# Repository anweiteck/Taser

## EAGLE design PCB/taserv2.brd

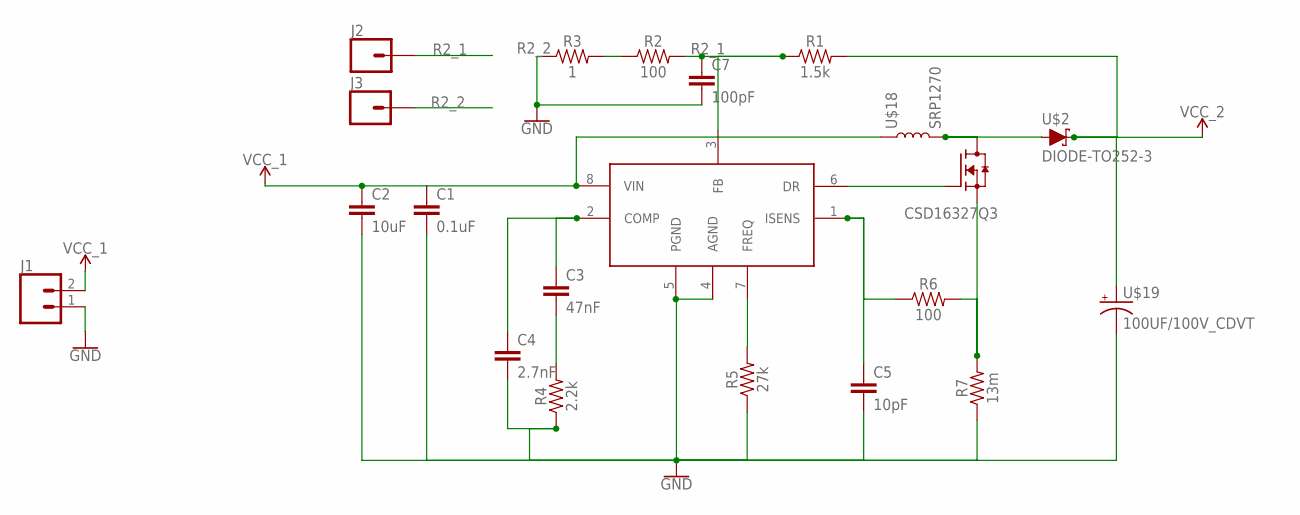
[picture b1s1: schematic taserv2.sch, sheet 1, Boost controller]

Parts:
C1: 0.1uF; 0603
C2: 10uF; 0603
C3: 47nF; 1206
C4: 2.7nF; 0603
C5: 10pF; 0603
C7: 100pF; 0603
J1: CONN_02LOCK; 1X02_LOCK
J2, J3: CONN_01; 1X01
Q1: CSD16327Q3; TRANS_CSD16327Q3
R1: 1.5k; 0603
R2, R6: 100; 0603
R3: 1; 0603
R4: 2.2k; 0603
R5: 27k; 0603
R7: 13m; 0603
U$1: LM3478; SOIC-8
U$2: DIODE-TO252-3; DPAK
U$18: SRP1270
U$19: 100UF/100V_CDVT

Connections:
GND: C1.2, C2.2, C4.2, C5.2, J1.1, R4.1, R5.1, R7.1, U$1.4 (AGND), U$1.5 (PGND), U$19.P$2 (-); also elsewhere on the board
unnamed: C3.1, C4.1, U$1.2 (COMP)
unnamed: C3.2, R4.2
unnamed: R5.2, U$1.7 (FREQ)
unnamed: R2.1, R3.2
unnamed: Q1.4 (G), U$1.6 (DR)
unnamed: Q1.1 (S), Q1.2 (S), Q1.3 (S), R6.2, R7.2
unnamed: C5.1, R6.1, U$1.1 (ISENS)
unnamed: Q1.5-8 (D), U$2.1 (A), U$2.3 (A), U$18.P$2 (2)
R2_1: C7.1, J2.1, R1.1, R2.2, U$1.3 (FB)
R2_2: C7.2, J3.1, R3.1
VCC_1: C1.1, C2.1, J1.2, U$1.8 (VIN), U$18.P$1 (1)
VCC_2: R1.2, U$2.4 (C), U$19.P$1 (+); also elsewhere on the board

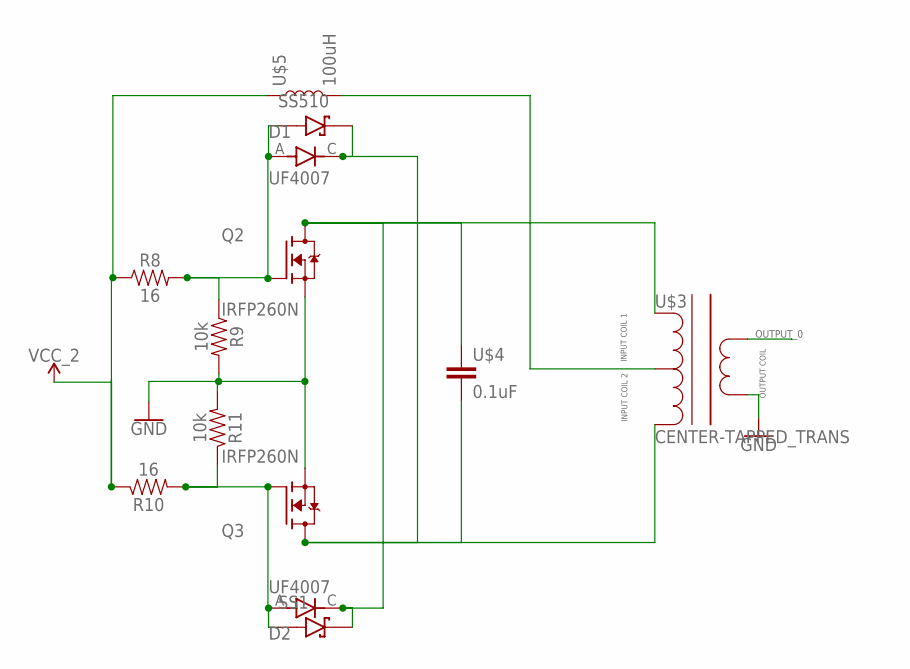
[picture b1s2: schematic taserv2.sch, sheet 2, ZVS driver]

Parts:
D1, D2: UF4007; DIOAD1036W78L520D274
Q2, Q3: IRFP260N; TO545P1560X500X2460-3
R8, R10: 16; 0603
R9, R11: 10k; 0603
SS1, SS510: MBRS340T3G; DIOM7959X261N
U$3: CENTER-TAPPED_TRANS
U$4: 0.1uF; MKP_CAP
U$5: 100uH; 1X04_LOCK

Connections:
GND: Q2.3 (S), Q3.3 (S), R9.2, R11.2, U$3.5; also elsewhere on the board
unnamed: D2.C (K), Q2.2 (D), SS1.C (K), U$3.3, U$4.1
unnamed: D1.A, Q2.1 (G), R8.2, R9.1, SS510.A
unnamed: D2.A, Q3.1 (G), R10.2, R11.1, SS1.A
unnamed: D1.C (K), Q3.2 (D), SS510.C (K), U$3.1, U$4.5 (2)
unnamed: U$3.2, U$5.4 (2)
OUTPUT_0: U$3.4; also elsewhere on the board
VCC_2: R8.1, R10.1, U$5.1; also elsewhere on the board

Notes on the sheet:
INPUT COIL 2
INPUT COIL 1
OUTPUT COIL

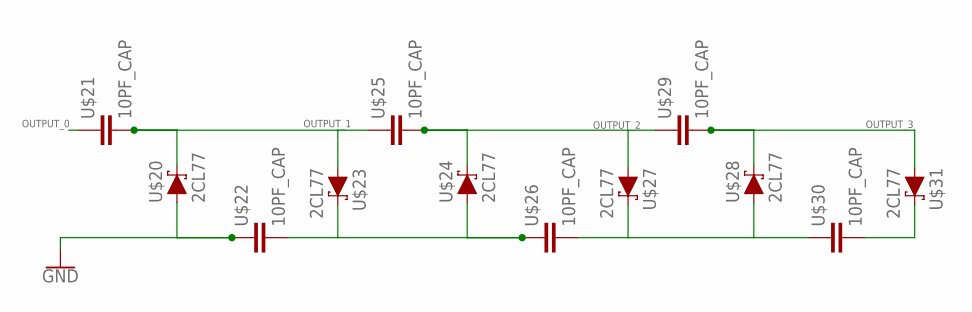
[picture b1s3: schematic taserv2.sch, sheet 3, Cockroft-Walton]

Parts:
U$20, U$23, U$24, U$27, U$28, U$31: 2CL77
U$21, U$22, U$25, U$26, U$29, U$30: 10PF_CAP

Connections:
GND: U$20.1 (A), U$22.1; also elsewhere on the board
unnamed: U$22.4 (2), U$23.4 (C), U$24.1 (A), U$26.1
unnamed: U$26.4 (2), U$27.4 (C), U$28.1 (A), U$30.1
unnamed: U$30.4 (2), U$31.4 (C)
OUTPUT_0: U$21.1; also elsewhere on the board
OUTPUT_1: U$20.4 (C), U$21.4 (2), U$23.1 (A), U$25.1
OUTPUT_2: U$24.4 (C), U$25.4 (2), U$27.1 (A), U$29.1
OUTPUT_3: U$28.4 (C), U$29.4 (2), U$31.1 (A)

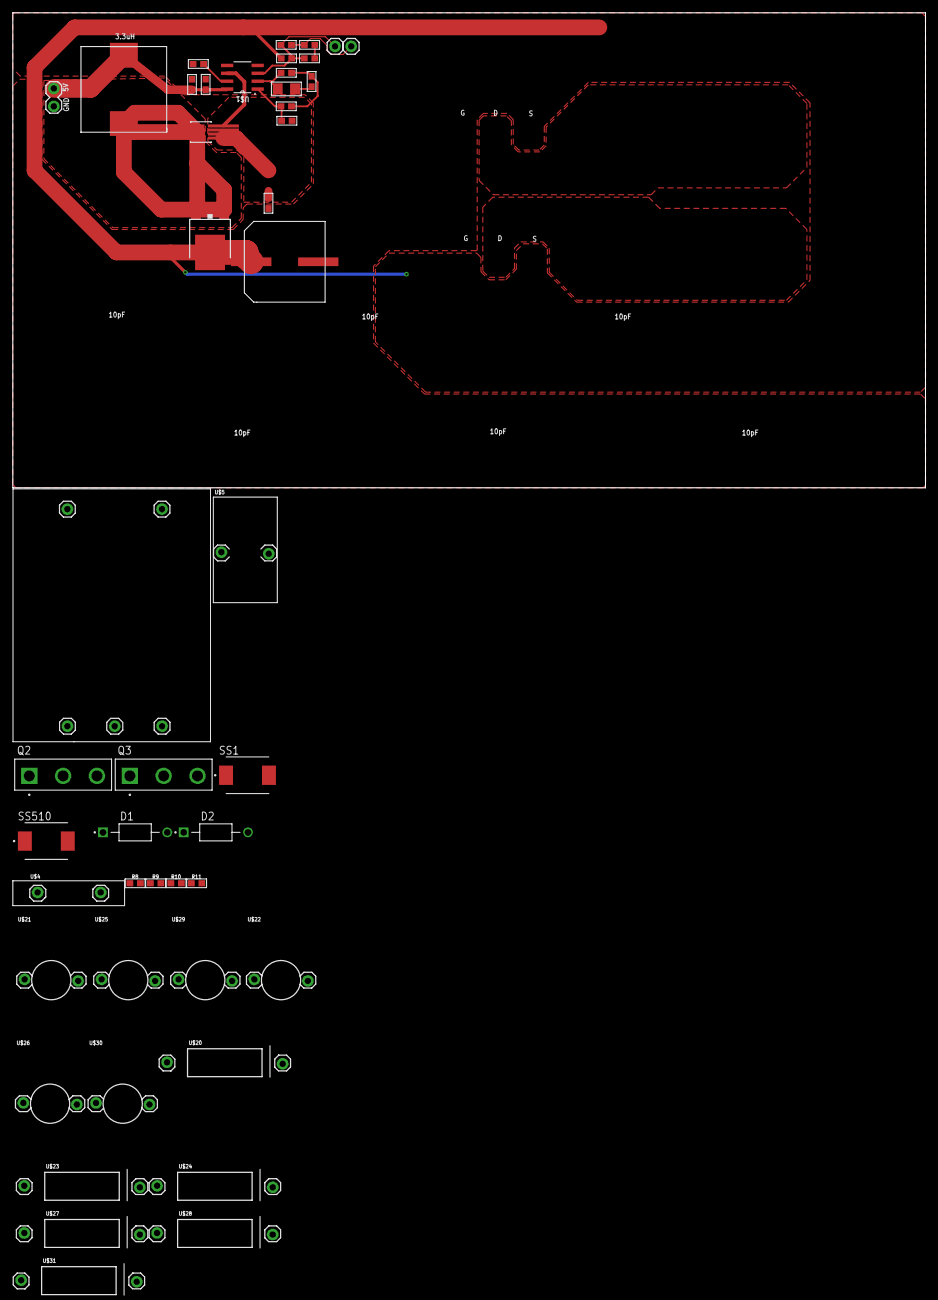
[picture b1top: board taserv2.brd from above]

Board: 2 copper layers, 147.0 x 76.5 mm, 46 parts (0 on the bottom side), 25 nets.

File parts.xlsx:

Part Type | Part name | Source | Unit Price (SGD) | Quantity | Delivery charge (SGD) | Total Price (SGD)
Boost controller 5V - 20V
Controller | LM3478 | Taobao | 0.31 | 5 | 0.64 | 2.19
N-channel MOSFET | CSD16327Q3 | Taobao | 0.49 | 5 | 0.69 | 3.14
Shottky Diode | SBRD10200 | Taobao | 0.41 | 4 | 0.92 | 2.56
Power Inductor | SRP1270 | Taobao | 3.19 | 3 | 2.2999999999999998 | 11.870000000000001
Resistor | 10mΩ 0603 resistor | Taobao | 0.69 | 10 | 0 | 0.69
Resistor | 1Ω 0603 resistor | - | 0 | 1 | 0 | 0
Resistor | 100Ω 0603 resistor | - | 0 | 2 | 0 | 0
Resistor | 1.5kΩ 0603 resistor | - | 0 | 1 | 0 | 0
Resistor | 2.2kΩ 0603 resistor | - | 0 | 1 | 0 | 0
Resistor | 27kΩ 0603 resistor | - | 0 | 1 | 0 | 0
Capacitor | 10pF 0603 capacitor | Taobao | 1.0900000000000001 | 100 | 0 | 1.0900000000000001
Capacitor | 100pF 0603 capacitor | Taobao | 0.87 | 100 | 0 | 0.87
Capacitor | 2.7nF 0603 capacitor | Taobao | 0.56999999999999995 | 50 | 0 | 0.56999999999999995
Capacitor | 47nF 1206 capacitor | Taobao | 0.92 | 50 | 0 | 0.92
Capacitor | 0.1uF 0603 capacitor | - | 0 | 1 | 0 | 0
Capacitor | 10uF 0603 capacitor | - | 0 | 1 | 0 | 0
Capacitor | 100uF 1206 capacitor | Taobao | 0.14000000000000001 | 10 | 0.92 | 2.3200000000000003
Subtotal |  |  |  |  |  | 26.220000000000006
ZVS driver
N-channel MOSFET | IRFP260 | Taobao | 0.76 | 4 | 0 | 3.04
Shottky diode | UF4007 | Taobao | 0.76 | 50 | 0 | 0.76
Power inductor | 100uH power inductor | - | 0 | 1 | 0 | 0
Resistor | 16Ω 0603 resistor | - | 0 | 2 | 0 | 0
Resistor | 10kΩ 0603 resistor | - | 0 | 2 | 0 | 0
Capacitor | 0.1uF MKP capacitor | - | 0 | 1 | 0 | 0
Transformer |  |  |  |  |  | 0
Subtotal |  |  |  |  |  | 3.8
Cockroft Walton generator
High voltage capacitor | 10pF 20kV capacitor | Taobao | 0.15 | 20 | 0.92 | 3.92
High voltage diode | 2CL77 | Taobao | 0.16 | 20 | 1.1499999999999999 | 4.3499999999999996
Subtotal |  |  |  |  |  | 8.27
Misclleaneous
offsets | offsets |  |  |  |  | 9
 |  |  |  |  | Total: | 29.290000000000006

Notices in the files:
parts and their libraries:
SparkFun-Capacitors: Licensing: Creative Commons ShareAlike 4.0 International - https://creativecommons.org/licenses/by-sa/4.0
